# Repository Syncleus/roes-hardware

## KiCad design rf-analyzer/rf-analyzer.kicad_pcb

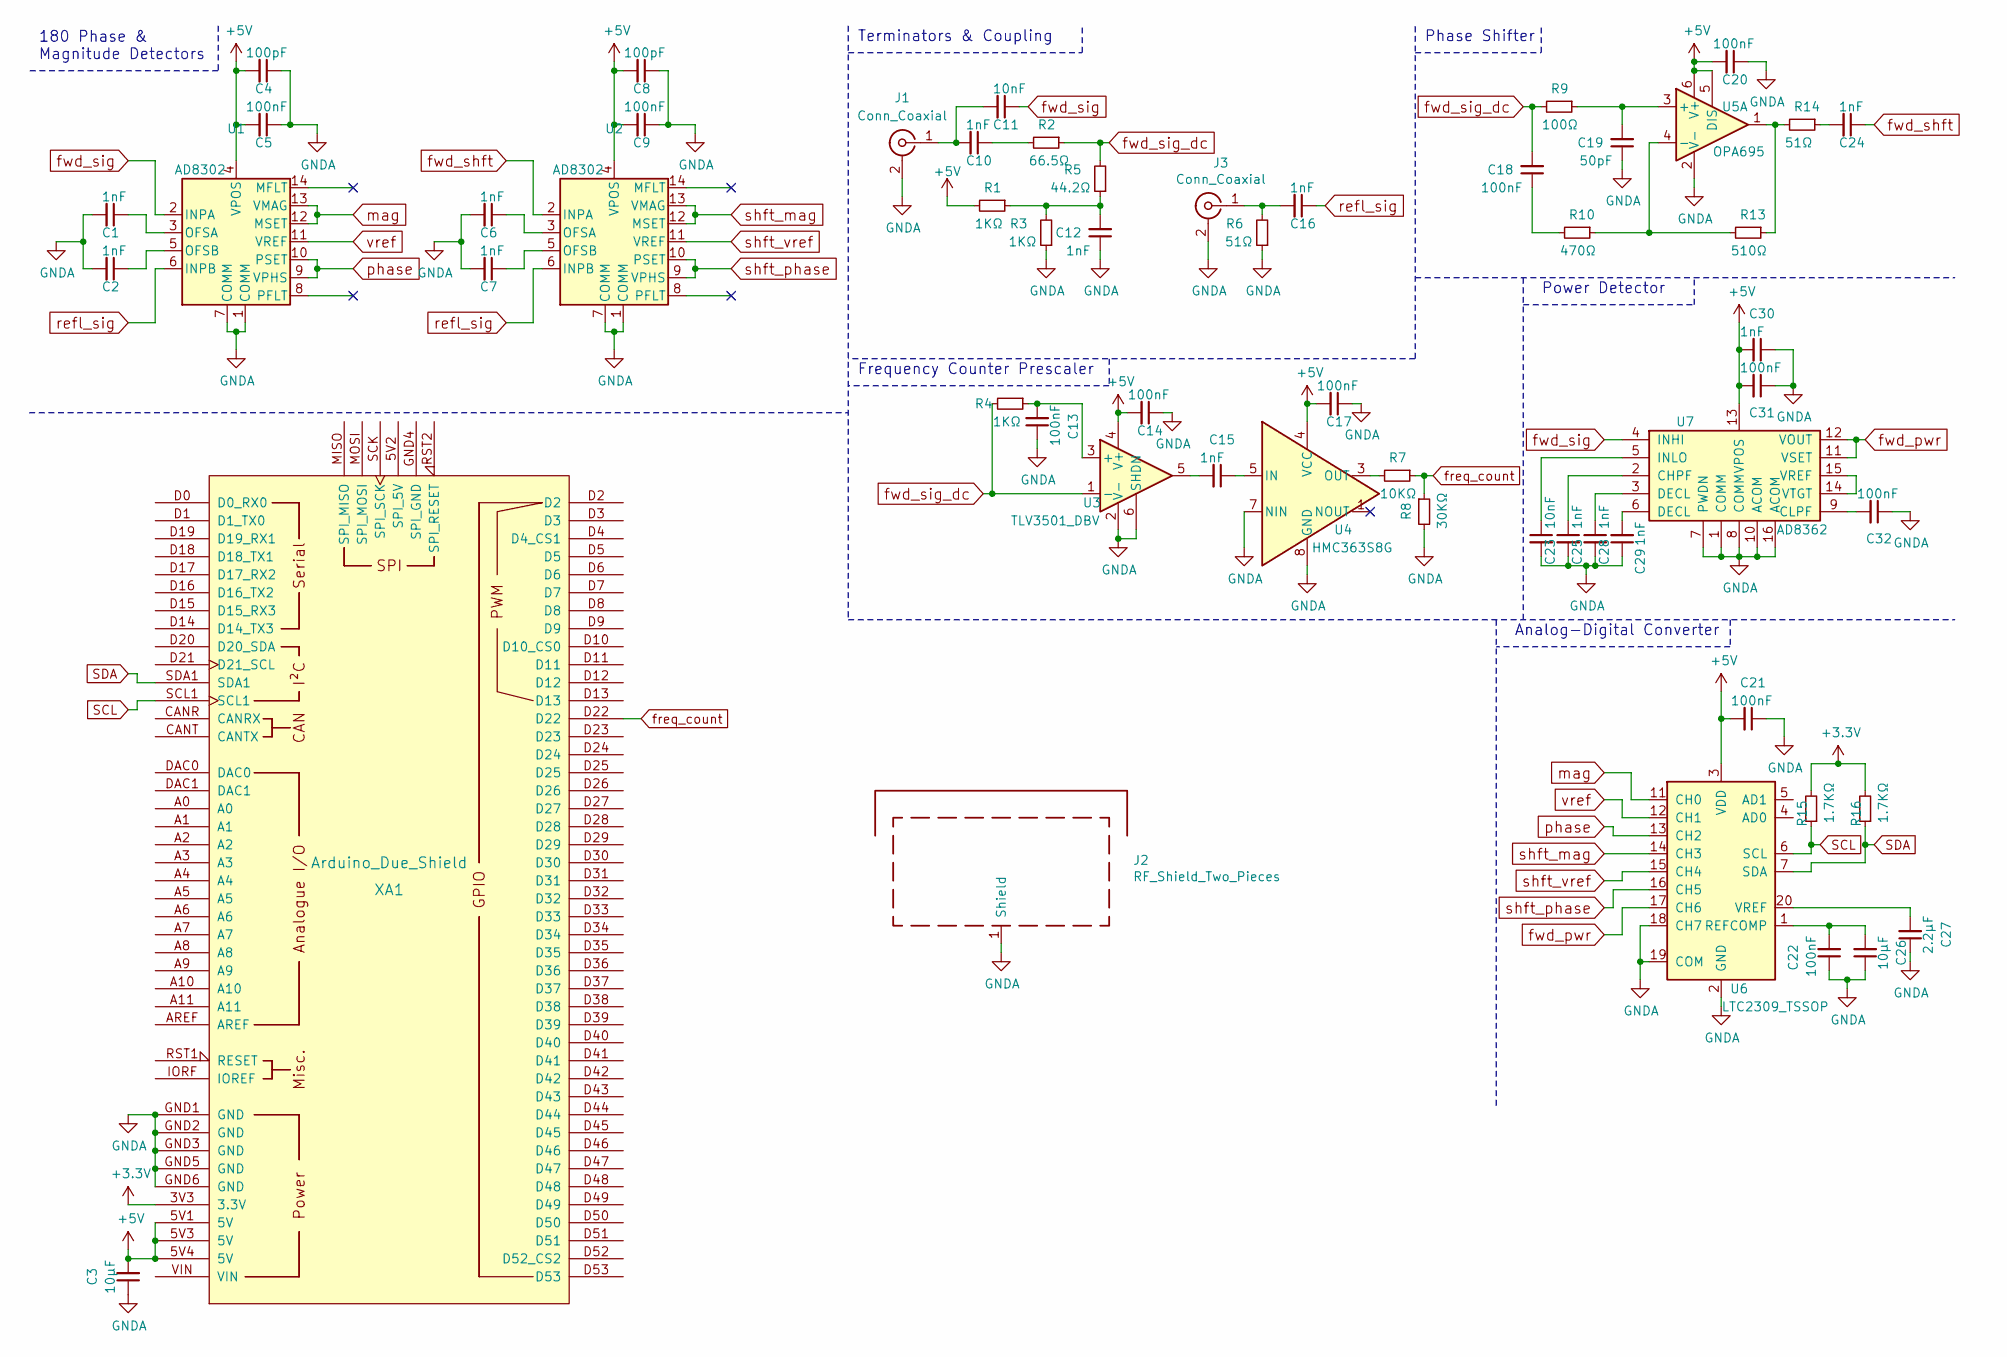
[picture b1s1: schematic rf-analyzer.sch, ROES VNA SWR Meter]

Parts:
C1, C2, C6, C7, C10, C12, C15, C16, C24, C25, C28, C29, C30: 1nF; C_0402_1005Metric
C3, C26: 10μF; C_0603_1608Metric
C4, C8: 100pF; C_0402_1005Metric
C5, C9, C13, C14, C17, C18, C20, C21, C22, C31, C32: 100nF; C_0402_1005Metric
C11, C23: 10nF; C_0402_1005Metric
C19: 50pF; C_0402_1005Metric
C27: 2.2μF; C_0402_1005Metric
J1, J3: Conn_Coaxial; SMA_Samtec_SMA-J-P-X-ST-EM1_EdgeMount
J2: RF_Shield_Two_Pieces; Laird_Technologies_BMI-S-230-F_50.8x38.1mm
R1, R3, R4: 1KΩ; C_0402_1005Metric
R2: 66.5Ω; C_0402_1005Metric
R5: 44.2Ω; C_0402_1005Metric
R6, R14: 51Ω; C_0402_1005Metric
R7: 10KΩ; C_0402_1005Metric
R8: 30KΩ; C_0402_1005Metric
R9: 100Ω; C_0402_1005Metric
R10: 470Ω; C_0402_1005Metric
R13: 510Ω; C_0402_1005Metric
R15, R16: 1.7KΩ; C_0402_1005Metric
U1, U2: AD8302; TSSOP-14_4.4x5mm_P0.65mm
U3: TLV3501_DBV; SOT-23-6
U4: HMC363S8G; SOIC-8_3.9x4.9mm_P1.27mm
U5: OPA695; SOT-23-6
U6: LTC2309_TSSOP; TSSOP-20_4.4x6.5mm_P0.65mm
U7: AD8362; TSSOP-16_4.4x5mm_P0.65mm
XA1: Arduino_Due_Shield

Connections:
+3V3: R15.2, R16.2, XA1.3V3 (3.3V)
+5V: C3.2, C4.2, C5.2, C8.2, C9.2, C14.2, C17.2, C20.2, C21.2, C30.2, C31.2, R1.2, U1.4 (VPOS), U2.4 (VPOS), U3.4 (V+), U4.4 (VCC), U5.5 (DIS), U5.6 (V+), U6.3 (VDD), U6.10 (VDD), U7.13 (VPOS), XA1.5V1 (5V), XA1.5V3 (5V), XA1.5V4 (5V)
GNDA: C1.2, C2.2, C3.1, C4.1, C5.1, C6.2, C7.2, C8.1, C9.1, C12.1, C13.1, C14.1, C17.1, C19.1, C20.1, C21.1, C22.1, C23.2, C25.2, C26.1, C27.1, C28.2, C29.1, C30.1, C31.1, C32.1, J1.2 (Ext), J2.1, J3.2 (Ext), R3.1, R6.1, R8.2, U1.1 (COMM), U1.7 (COMM), U2.1 (COMM), U2.7 (COMM), U3.2 (V-), U3.6 (SHDN), U4.7 (NIN), U4.8 (GND), U5.2 (V-), U6.2 (GND), U6.8 (GND), U6.9 (GND), U6.18 (CH7), U6.19 (COM), U7.1 (COMM), U7.7 (PWDN), U7.8 (COMM), U7.10 (ACOM), U7.16 (ACOM), XA1.GND1 (GND), XA1.GND2 (GND), XA1.GND3 (GND), XA1.GND5 (GND), XA1.GND6 (GND)
unnamed: C1.1, U1.3 (OFSA)
unnamed: C2.1, U1.5 (OFSB)
unnamed: C6.1, U2.3 (OFSA)
unnamed: C7.1, U2.5 (OFSB)
unnamed: C10.1, R2.2
unnamed: C10.2, C11.2, J1.1 (In)
unnamed: C12.2, R1.1, R3.2, R5.1
unnamed: C13.2, R4.1, U3.3 (+)
unnamed: C15.1, U4.5 (IN)
unnamed: C15.2, U3.5
unnamed: C16.2, J3.1 (In), R6.2
unnamed: C18.1, R10.2
unnamed: C19.2, R9.1, U5.3 (+)
unnamed: C22.2, C26.2, U6.1 (REFCOMP)
unnamed: C23.1, U7.5 (INLO)
unnamed: C24.2, R14.1
unnamed: C25.1, U7.2 (CHPF)
unnamed: C27.2, U6.20 (VREF)
unnamed: C28.1, U7.3 (DECL)
unnamed: C29.2, U7.6 (DECL)
unnamed: C32.2, U7.9 (CLPF)
unnamed: R7.2, U4.3 (OUT)
unnamed: R10.1, R13.2, U5.4 (-)
unnamed: R13.1, R14.2, U5.1
unnamed: U7.14 (VTGT), U7.15 (VREF)
SCL: R15.1, U6.6 (SCL), XA1.SCL1
SDA: R16.1, U6.7 (SDA), XA1.SDA1
freq_count: R7.1, R8.1, XA1.D22
fwd_pwr: U6.17 (CH6), U7.11 (VSET), U7.12 (VOUT)
fwd_shft: C24.1, U2.2 (INPA)
fwd_sig: C11.1, U1.2 (INPA), U7.4 (INHI)
fwd_sig_dc: C18.2, R2.1, R4.2, R5.2, R9.2, U3.1 (-)
mag: U1.12 (MSET), U1.13 (VMAG), U6.11 (CH0)
phase: U1.9 (VPHS), U1.10 (PSET), U6.13 (CH2)
refl_sig: C16.1, U1.6 (INPB), U2.6 (INPB)
shft_mag: U2.12 (MSET), U2.13 (VMAG), U6.14 (CH3)
shft_phase: U2.9 (VPHS), U2.10 (PSET), U6.16 (CH5)
shft_vref: U2.11 (VREF), U6.15 (CH4)
vref: U1.11 (VREF), U6.12 (CH1)

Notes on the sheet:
Phase Shifter
Power Detector
180 Phase & Magnitude Detectors
Terminators & Coupling
Analog-Digital Converter
Frequency Counter Prescaler

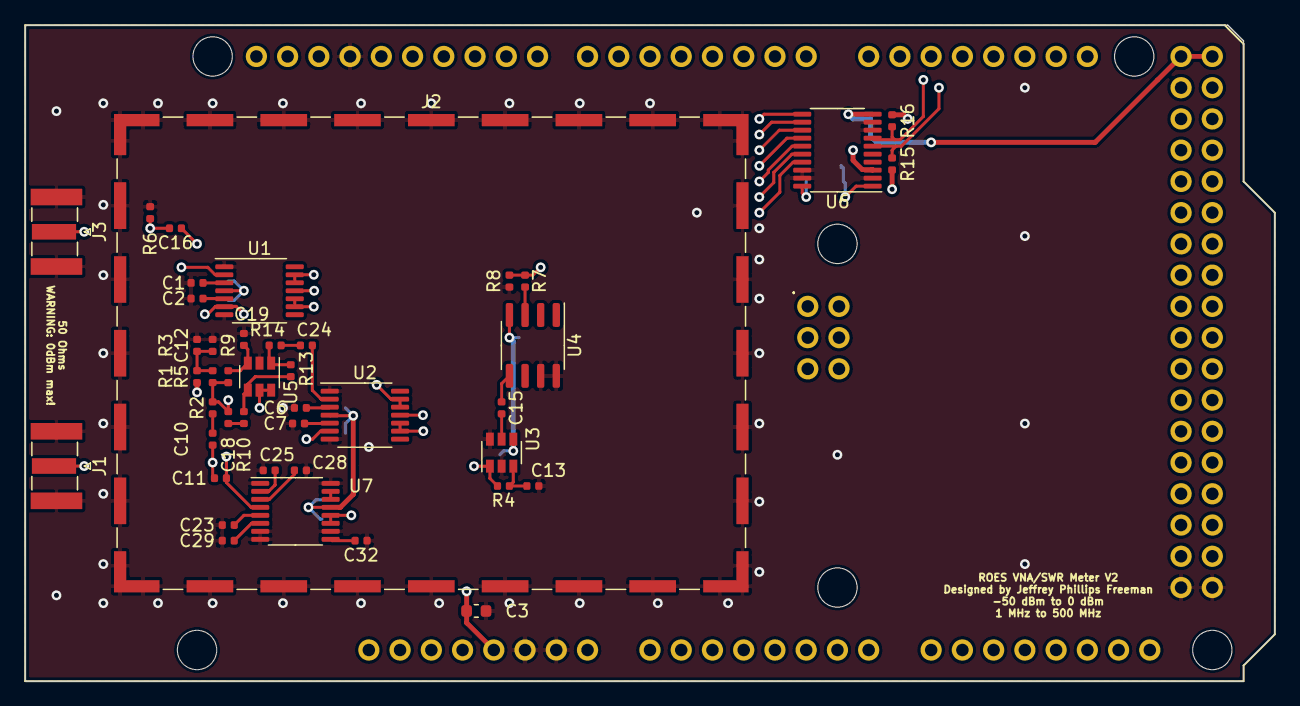
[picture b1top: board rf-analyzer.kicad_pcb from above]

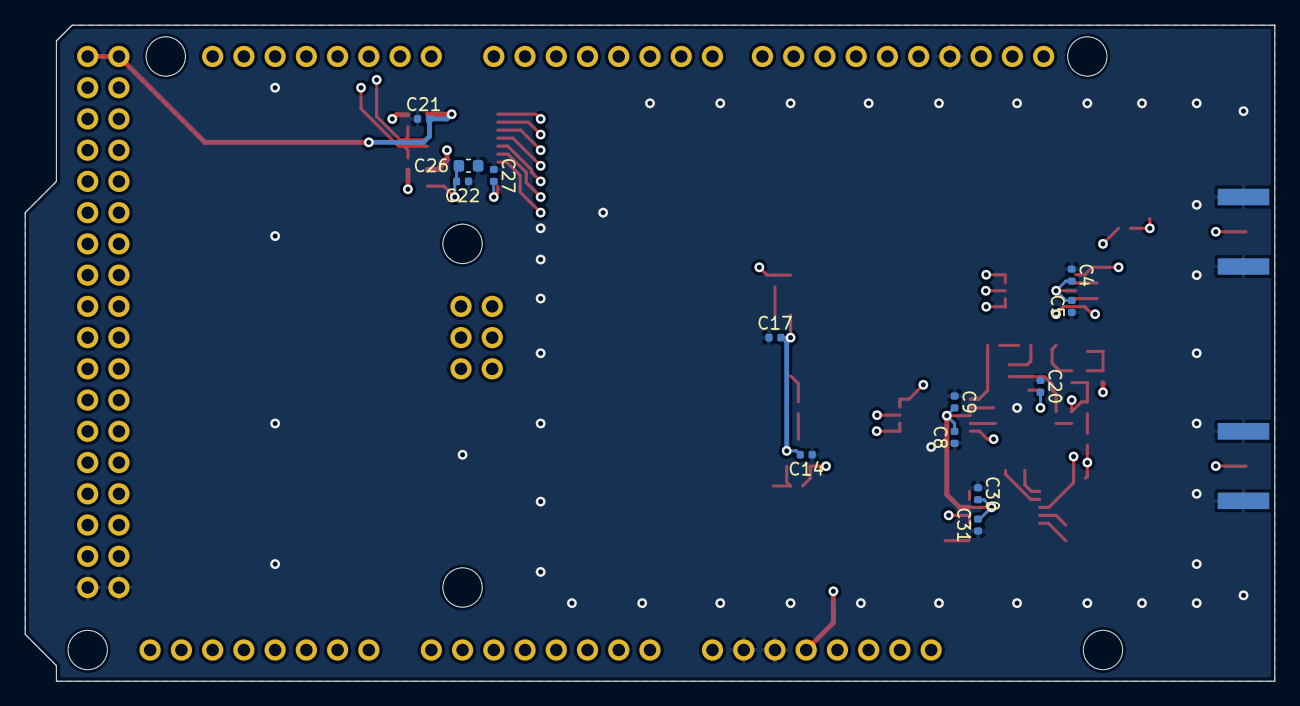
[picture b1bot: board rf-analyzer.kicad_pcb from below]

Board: 4 copper layers, 101.6 x 53.3 mm, 57 parts (13 on the bottom side), 42 nets.

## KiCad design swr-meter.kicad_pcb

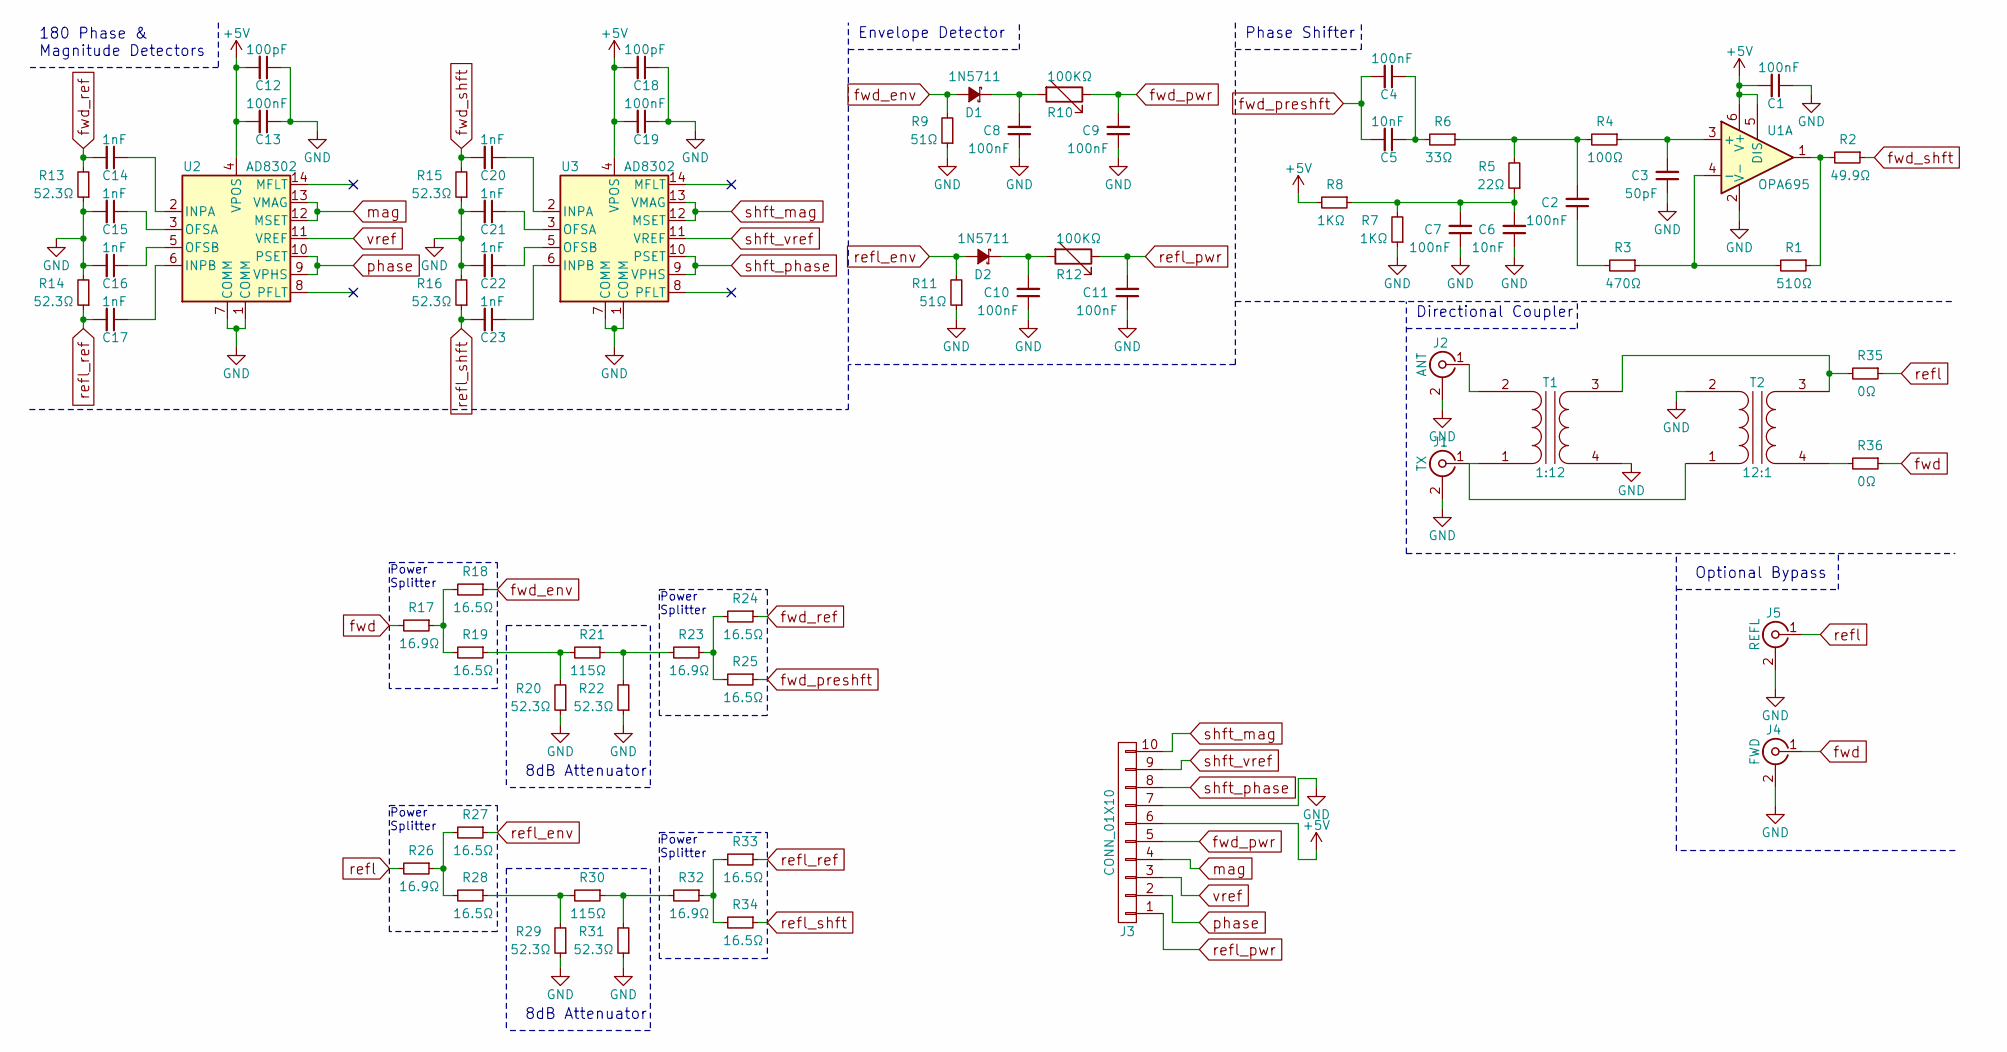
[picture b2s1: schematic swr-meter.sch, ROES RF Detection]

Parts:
C1, C2, C4, C7, C8, C9, C10, C11, C13, C19: 100nF; C_0603_HandSoldering
C3: 50pF; C_0603_HandSoldering
C5, C6: 10nF; C_0603_HandSoldering
C12, C18: 100pF; C_0603_HandSoldering
C14, C15, C16, C17, C20, C21, C22, C23: 1nF; C_0603_HandSoldering
D1, D2: 1N5711; D_DO-35_SOD27_P12.70mm_Horizontal
J1: TX; SMA_THT_Jack_Straight
J2: ANT; SMA_THT_Jack_Straight
J3: CONN_01X10; Pin_Header_Straight_1x10_Pitch2.00mm
J4: FWD; U.FL-COAX
J5: REFL; U.FL-COAX
R1: 510Ω; R_0603_HandSoldering
R2: 49.9Ω; R_0603
R3: 470Ω; R_0603_HandSoldering
R4: 100Ω; R_0603_HandSoldering
R5: 22Ω; R_0603_HandSoldering
R6: 33Ω; R_0603_HandSoldering
R7, R8: 1KΩ; R_0603_HandSoldering
R9, R11: 51Ω; R_0603_HandSoldering
R10, R12: 100KΩ; R_0603_HandSoldering
R13, R14, R15, R16, R20, R22, R29, R31: 52.3Ω; R_0603_HandSoldering
R17, R23, R26, R32: 16.9Ω; R_0603_HandSoldering
R18, R19, R24, R25, R27, R28, R33, R34: 16.5Ω; R_0603_HandSoldering
R21, R30: 115Ω; R_0603_HandSoldering
R35, R36: 0Ω; R_0603_HandSoldering
T1: 1:12; L_Toroid_Vertical_L35.6mm_W17.8mm_P12.70mm_Pulse_E_transform
T2: 12:1; L_Toroid_Vertical_L35.6mm_W17.8mm_P12.70mm_Pulse_E_transform
U1: OPA695; SOT-23-6
U2, U3: AD8302; TSSOP-14_4.4x5mm_Pitch0.65mm

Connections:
+5V: C1.2, C12.2, C13.2, C18.2, C19.2, J3.6, R8.2, U1.5 (DIS), U1.6 (V+), U2.4 (VPOS), U3.4 (VPOS)
GND: C1.1, C3.1, C6.1, C7.1, C8.1, C9.1, C10.1, C11.1, C12.1, C13.1, C15.2, C16.2, C18.1, C19.1, C21.2, C22.2, J1.2 (Ext), J2.2 (Ext), J3.7, J4.2 (Ext), J5.2 (Ext), R7.1, R9.1, R11.1, R13.1, R14.2, R15.1, R16.2, R20.1, R22.1, R29.1, R31.1, T1.4 (SB), T2.2 (AB), U1.2 (V-), U2.1 (COMM), U2.7 (COMM), U3.1 (COMM), U3.7 (COMM)
unnamed: C2.1, R3.2
unnamed: C2.2, R4.2, R5.2, R6.1
unnamed: C3.2, R4.1, U1.3 (+)
unnamed: C4.1, C5.1, R6.2
unnamed: C6.2, C7.2, R5.1, R7.2, R8.1
unnamed: C8.2, D1.1 (K), R10.2
unnamed: C10.2, D2.1 (K), R12.2
unnamed: C14.1, U2.2 (INPA)
unnamed: C15.1, U2.3 (OFSA)
unnamed: C16.1, U2.5 (OFSB)
unnamed: C17.1, U2.6 (INPB)
unnamed: C20.1, U3.2 (INPA)
unnamed: C21.1, U3.3 (OFSA)
unnamed: C22.1, U3.5 (OFSB)
unnamed: C23.1, U3.6 (INPB)
unnamed: J1.1 (In), T1.1 (AA), T2.1 (AA)
unnamed: J2.1 (In), T1.2 (AB)
unnamed: R1.1, R2.2, U1.1
unnamed: R1.2, R3.1, U1.4 (-)
unnamed: R17.1, R18.2, R19.2
unnamed: R19.1, R20.2, R21.2
unnamed: R21.1, R22.2, R23.2
unnamed: R23.1, R24.2, R25.2
unnamed: R26.1, R27.2, R28.2
unnamed: R28.1, R29.2, R30.2
unnamed: R30.1, R31.2, R32.2
unnamed: R32.1, R33.2, R34.2
unnamed: R35.2, T1.3 (SA), T2.3 (SA)
unnamed: R36.2, T2.4 (SB)
fwd: J4.1 (In), R17.2, R36.1
fwd_env: D1.2 (A), R9.2, R18.1
fwd_preshft: C4.2, C5.2, R25.1
fwd_pwr: C9.2, J3.5, R10.1
fwd_ref: C14.2, R13.2, R24.1
fwd_shft: C20.2, R2.1, R15.2
mag: J3.4, U2.12 (MSET), U2.13 (VMAG)
phase: J3.2, U2.9 (VPHS), U2.10 (PSET)
refl: J5.1 (In), R26.2, R35.1
refl_env: D2.2 (A), R11.2, R27.1
refl_pwr: C11.2, J3.1, R12.1
refl_ref: C17.2, R14.1, R33.1
refl_shft: C23.2, R16.1, R34.1
shft_mag: J3.10, U3.12 (MSET), U3.13 (VMAG)
shft_phase: J3.8, U3.9 (VPHS), U3.10 (PSET)
shft_vref: J3.9, U3.11 (VREF)
vref: J3.3, U2.11 (VREF)

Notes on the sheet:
Phase Shifter
Envelope Detector
180 Phase & Magnitude Detectors
Directional Coupler
Power Splitter
8dB Attenuator
Optional Bypass

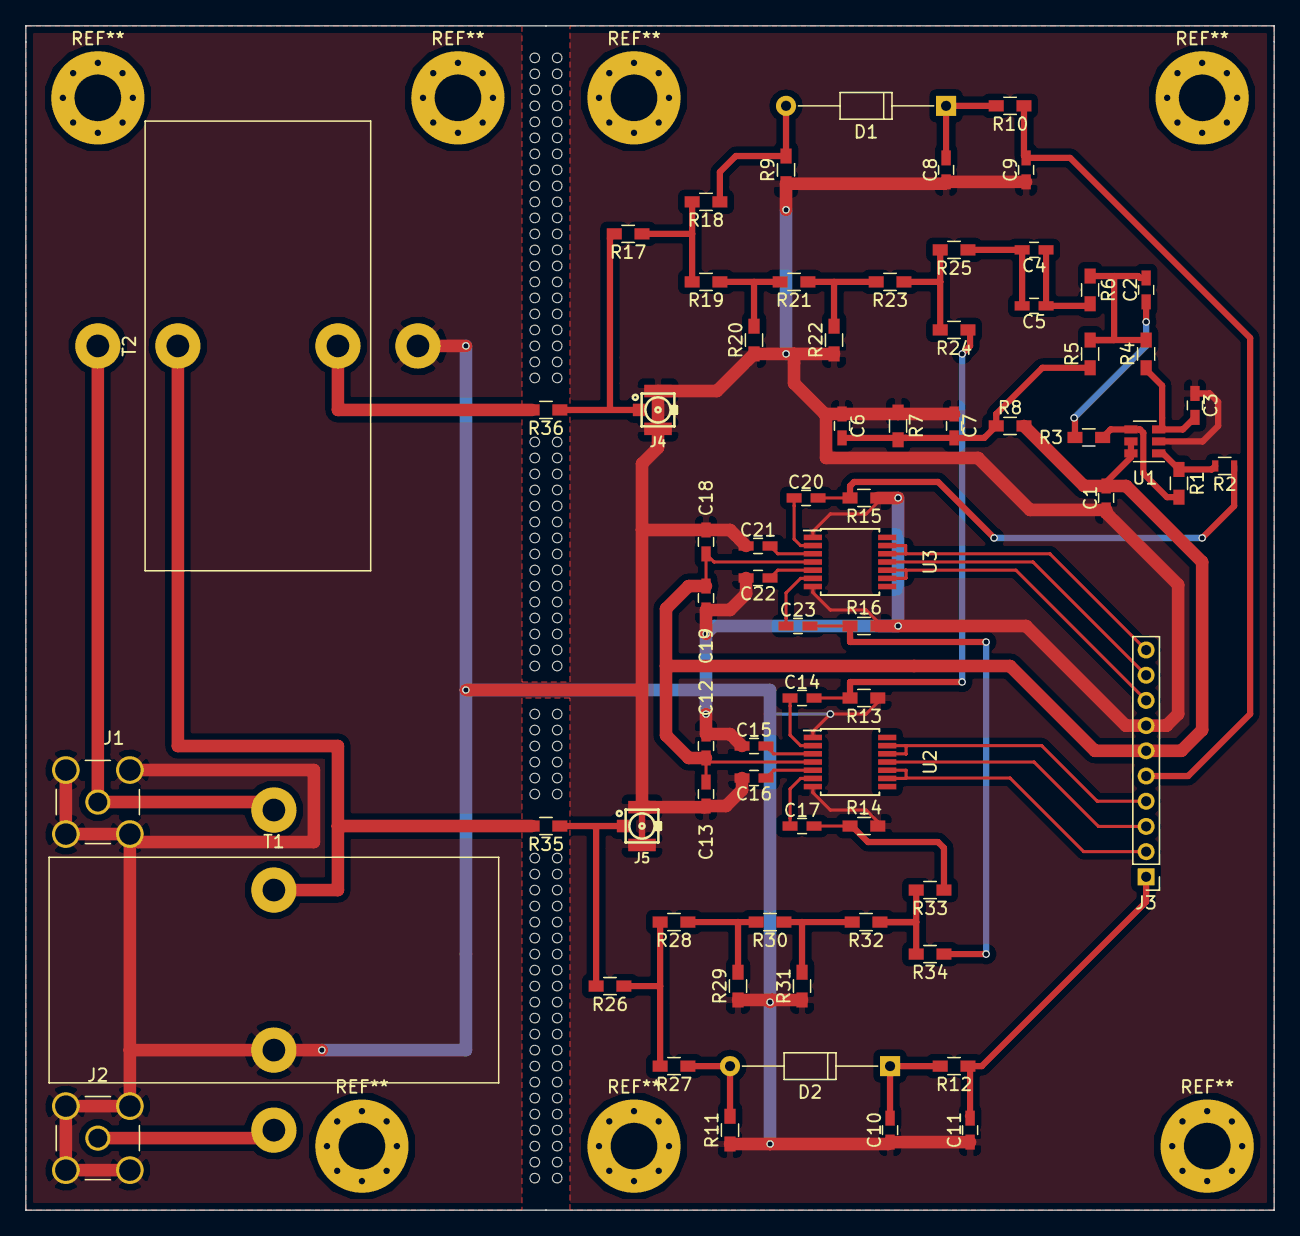
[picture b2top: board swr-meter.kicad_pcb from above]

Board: 2 copper layers, 99.1 x 94.0 mm, 71 parts (0 on the bottom side), 48 nets.

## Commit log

2017-07-21 Initial working version of the ROES RF section, revision 0.1.
2019-01-02 Adding cache file for lib.
2019-01-02 Updated resistors to larger sizes for more power.
2019-01-03 Got the old schematic imported
2019-01-03 Added and cleaned up DC schematic.
2020-08-27 cleaned up schematic to use proper library symbols.
2020-08-27 Added Schematic metadata such as title.
2020-08-27 Updated gitignore to exlude all backup files.
2020-08-27 Moved a drawing line that was somehow misplaced.
2020-08-27 Removed LMX2322 from schematic.
2020-08-27 Updated power rails to be safer for the arduino Due.
2020-09-01 Revert "Updated power rails to be safer for the arduino Due."
    This reverts commit 4777d5e6577dfa59df44698bd1e5544e157ec2ab.
2020-09-01 Eliminated power splitters and attenuator.
2020-09-01 Cleaned up the ADC.
2020-09-01 Minor tweak to make phase shifter fit in the schematic.
2020-09-01 Associated correct footprint with Due shield in schematic.
2020-09-01 Fixed powerrails to use all pins on Due shield.
2020-09-01 Added frequency counter front-end.
2020-09-01 Made fall correction to power rails.
2020-09-01 Added frequency counter prescaler.
2020-09-01 Removed decoupling capacitor from prescaler.
2020-09-01 Added the decoupling caps in a central location allowing me to reduce the overall number of capacitors.
2020-09-01 Added shielding to schematic.
2020-09-01 Added a missing wire to a power rail.
2020-09-01 Added some missing bypass capacitors.
2020-09-01 Moved label so it didnt overlap.
2020-09-01 Removed the enumeration of the components, will re-add later5.
2020-09-02 Fixed bug in envelope detector that messed up DC decoupling.
2020-09-02 Reduced the number and value of the decoupling capacitors on the DC biasing section.
2020-09-02 moved tank on powerrail to new location.
2020-09-02 Replaced the zener with a voltage divder for better frequency response.
2020-09-02 moved around a power rail that was outside of the border.
2020-09-04 Updated footprints in schematic to match new minarturized design.
2020-09-04 Becgan populating the PCB.
2020-09-04 Upgraded power detection to use more accurate IC based true RMS.
2020-09-04 Added some additional design notes.
2020-09-04 Grounded a floating pin.
2020-09-04 Fixed incorrect ground point.
2020-09-04 Populated and routed PCB board.
2020-09-04 Added some vias to ensure all layers are filled with a ground plane.
2020-09-04 Added some silkscreen info.
2020-09-04 Moved around SMA connectors to pass inspection.
2020-09-04 Changed position of graphical lines on schematic.
2020-09-04 Final version of PCB.
2020-09-04 Some minor fixes before printing V2 PCB.
2020-09-04 Releasing version 2.0 of ROES.
2020-09-05 Added some design notes to schematic.
2020-09-05 Adding cache lib for directional coupler.
2020-09-05 Moved one of the notes to be more visible.
2020-09-05 Minor adjustment to terminator resistor values.
